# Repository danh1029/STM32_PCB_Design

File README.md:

# MyPCB Project

## Description
STM32f103 PCB designed using KiCad.
First project to approaching hardware design

## Hardware
- MCU: STM32f103c8t6
- Input Voltage: Ouput peripheral, USB
- Communication: I2C, SPI, UART

## Software
- KiCad 9.0

## Author
This project desgin base on Phil'LAB Udemy Course

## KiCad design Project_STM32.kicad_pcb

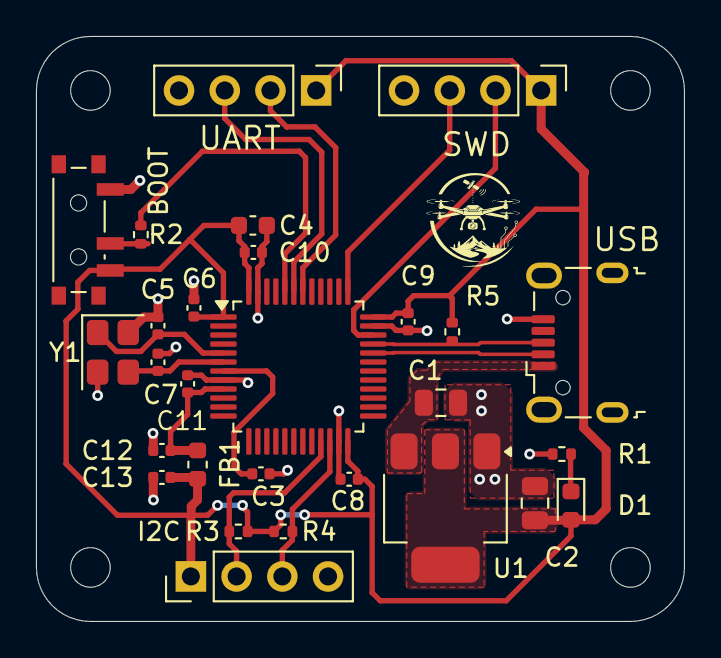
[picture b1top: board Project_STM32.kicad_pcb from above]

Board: 2 copper layers, 36.0 x 32.5 mm, 32 parts (0 on the bottom side), 18 nets.

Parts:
BOOT: SW_SPDT; SW_SPDT_PCM12
C1, C2: 22u; C_0805_2012Metric
C3, C6, C8, C9, C10: 100n; C_0402_1005Metric
C4: 10u; C_0603_1608Metric
C5, C7: 10pF; C_0402_1005Metric
C11: 10n; C_0402_1005Metric
C12, C13: 1u; C_0402_1005Metric
D1: RED; LED_0603_1608Metric
FB1: 120R; L_0603_1608Metric
H1, H2, H3, H4: MountingHole; MountingHole_2.2mm_M2
I2C: Conn_01x04_Pin; PinHeader_1x04_P2.54mm_Vertical
R1, R3, R4, R5: 1k5; R_0402_1005Metric
R2: 10K; R_0402_1005Metric
SWD: Conn_01x04_Pin; PinHeader_1x04_P2.54mm_Vertical
U1: AMS1117-3.3; SOT-223-3_TabPin2
U2: STM32F103C8Tx; LQFP-48_7x7mm_P0.5mm
UART: Conn_01x04_Pin; PinHeader_1x04_P2.54mm_Vertical
USB: USB_B_Micro; USB_Micro-B_Wuerth_629105150521
Y1: 16MHz; Crystal_SMD_3225-4Pin_3.2x2.5mm

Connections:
+3.3V: BOOT.3 (C), C2.1, C4.1, C6.1, C8.1, C9.1, C10.1, C13.1, D1.2 (A), FB1.2, I2C.1, R3.1, R4.1, R5.1, SWD.1, U1.2 (VO), U2.1 (VBAT), U2.24 (VDD), U2.36 (VDD), U2.48 (VDD), UART.1
+3.3VA: C11.1, C12.1, FB1.1, U2.9 (VDDA)
/BOOT0: R2.2, U2.44 (BOOT0)
/HSE_IN: C5.1, U2.5 (PD0), Y1.1
/HSE_OUT: C7.1, U2.6 (PD1), Y1.3
/I2C2_CDA: I2C.3, R4.2, U2.22 (PB11)
/I2C2_SCL: I2C.2, R3.2, U2.21 (PB10)
/NRST: C3.1, U2.7 (NRST)
/SWCLK: SWD.3, U2.37 (PA14)
/SWDIO: SWD.2, U2.34 (PA13)
/SW_BOOT0: BOOT.2 (B), R2.1
/USART1_RX: U2.43 (PB7), UART.3
/USART1_TX: U2.42 (PB6), UART.2
/USB_D+: R5.2, U2.33 (PA12), USB.3 (D+)
/USB_D-: U2.32 (PA11), USB.2 (D-)
GND: BOOT.1 (A), C1.2, C2.2, C3.2, C4.2, C5.2, C6.2, C7.2, C8.2, C9.2, C10.2, C11.2, C12.2, C13.2, I2C.4, R1.2, SWD.4, U1.1 (GND), U2.8 (VSSA), U2.23 (VSS), U2.35 (VSS), U2.47 (VSS), UART.4, USB.5 (GND), Y1.2 (G), Y1.4 (G)
unnamed: D1.1 (K), R1.1
VBUS: C1.1, U1.3 (VI), USB.1 (VBUS)
